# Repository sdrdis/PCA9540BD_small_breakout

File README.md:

# PCA9540BD small breakout board #
 
Schematics for a small breakout board PCA9540BD component (http://www.nxp.com/documents/data_sheet/PCA9540B.pdf).

## About the PCA9540BD ##

The PCA9540BD is a 2-channel I2C-bus multiplexer.

Let's say that you want to get data from 2 components through I2C but they both have the same I2C address. The PCA9540BD allows you to redirect the SCA and SDA pins to (SCA0, SDA0) or (SCA1, SDA1).

## About this breakout board ##

The PCA9540BD pins have a pitch of 0.05 inches making the component difficult to connect to your arduino. This breakout board allows you to connect the PCA9540BD component to a classical prototype board.

It can conveniently be connected in the middle of the board. Unlike a DIP8 connector, the order of the pins are altered so that
all pins connected to your arduino are on one side, and all pins connected to your devices are on the other side.

You can see below how the pins are ordered:

The schematics are under the GPLv3+ license.

## Library for arduino ##

I have implemented a driver for arduino allowing you to control the component. It is available in this [repository](https://github.com/sdrdis/PCA9540BD).

## About the author ##

[See the blog post about the project.](http://sebastien.drouyer.com/projects/pca9540bd-driver-for-arduino-breakout-boards-schematics.html)

Sebastien Drouyer - [website](http://sebastien.drouyer.com) - [twitter](https://twitter.com/sdrdis)

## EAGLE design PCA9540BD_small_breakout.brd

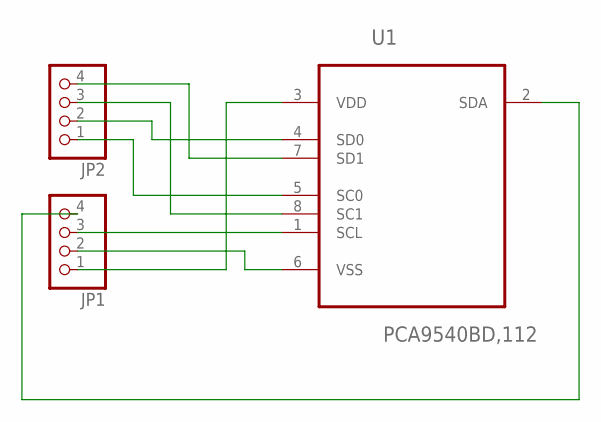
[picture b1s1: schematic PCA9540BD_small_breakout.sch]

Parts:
JP1, JP2: PINHD-1X4; 1X04
U1: PCA9540BD,112; SOIC127P600X175-8N

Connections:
unnamed: JP1.1, U1.3 (VDD)
unnamed: JP1.2, U1.6 (VSS)
unnamed: JP1.3, U1.1 (SCL)
unnamed: JP1.4, U1.2 (SDA)
unnamed: JP2.1, U1.5 (SC0)
unnamed: JP2.2, U1.4 (SD0)
unnamed: JP2.3, U1.8 (SC1)
unnamed: JP2.4, U1.7 (SD1)

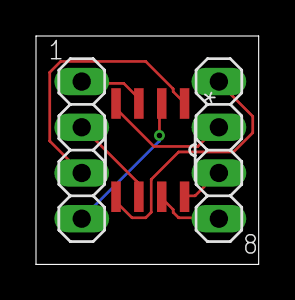
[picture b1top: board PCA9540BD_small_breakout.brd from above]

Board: 2 copper layers, 12.4 x 12.7 mm, 3 parts (0 on the bottom side), 8 nets.

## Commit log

2015-11-13 added image
2015-11-13 added image breakout board middle
2015-11-13 added pins order
2015-11-15 Added a link to the blog post.
